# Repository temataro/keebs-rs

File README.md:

# Keebs 'R Us

Informal notes on me learning how to actually make this.
If you read this and you're not me, pretend you didn't.

The project template for the `rp2040-hal` is good.

To flash the code onto the uC, `probe-rs` is used.
  We'll just copy it over the old fashioned way since I don't have a debug probe.

Probes can translate from the USB/Ethernet interface on your computer to the
target interface.
(SWD for ARM, JTAG for ?..., etc)

_____________________________________________________________
We'll be using `elf2uf2-rs` which will convert the `.elf` file we generate to
binary targets for the cortex-m0+ uC. Loading a `.uf2` over USB.

Hold down the `BOOT` button on the uC while connecting to the PC and upload.
The pico should automatically get mounted on Linux.
It's found in `/run/media/tem`

> [!IMPORTANT]
> Go to `.cargo/config` and change the default runner 

#### <callout> `.cargo/config.toml`
```toml
[target.`cfg(all(target-arch = "arm", target_os = "none"))`]
runner = "elf2uf2-rs -d"
```

_____________________________________________________________
(Alternate): Look into `picotool`. The `elf` produced by Rust should be compatible
with the output that it takes. Just append a `.elf` to the binary.

### Requirements:

* rustup
* thumbv6m-none-eabi toolchain
* elf2uf2-rs

### Bare minimum file structure in your project

```
.
|-> Cargo.toml
|-> .cargo/
    |-> config.toml
|
|-> src/
    |-> main.rs
```

```shell
rustup target install thumbv6m-none-eabi
cargo install --locked elf2uf2-rs
```

Running:
`cargo run` - debug build
`cargo run --release` - release build (Our runner (`elf2uf2-rs`) will build and
copy it to the RP2040.)

## Bootloader

So apparently there's a bootloader, and to write 256 bytes to it, we need to initialize
it. Use this snippet to do so.

#### <callout> `src/main.rs`
```rust
use rp2040_boot2;
#[link_section = ".boot2"]
#[used]
pub static BOOT_LOADER: [u8; 256] = rp2040_boot2::BOOT_LOADER_W25Q080;
```

## Cargo.toml

#### <callout> `Cargo.toml`
```toml
[package]
edition = "2021"
# We're using 2021 because `cargo build` errors with 2024. No stable version exists.
name = "Keebs-rs"
version = "0.1.0"
license = "MIT OR Apache-2.0"
author = "Tem soon but for now this is all rp-hal code..."

[dependencies]
cortex-m = "0.7"
cortex-m-rt = "0.7"
embedded-hal = { version = "1.0.0" }
rp2040-hal = { version="0.10", features=["rt", "critical-section-impl"] }
rp2040-boot2 = "0.3.0"
panic-halt = "0.2.0"

defmt = "0.3"
defmt-rtt = "0.4"
panic-probe = { version = "0.3", features = ["print-defmt"] }

rp-pico = "0.9"

# cargo build/run
[profile.dev]
codegen-units = 1
debug = 2
debug-assertions = true
incremental = false
opt-level = 3
overflow-checks = true

# cargo build/run --release
[profile.release]
codegen-units = 1
debug = 2
debug-assertions = false
incremental = false
lto = 'fat'
opt-level = 3
overflow-checks = false

# do not optimize proc-macro crates = faster builds from scratch
[profile.dev.build-override]
codegen-units = 8
debug = false
debug-assertions = false
opt-level = 0
overflow-checks = false

[profile.release.build-override]
codegen-units = 8
debug = false
debug-assertions = false
opt-level = 0
overflow-checks = false

# cargo test
[profile.test]
codegen-units = 1
debug = 2
debug-assertions = true
incremental = false
opt-level = 3
overflow-checks = true

# cargo test --release
[profile.bench]
codegen-units = 1
debug = 2
debug-assertions = false
incremental = false
lto = 'fat'
opt-level = 3
```

## The Bare Minimum to Include

Goal: GPIO25 is the onboard green LED.
Make blinky.

Req. 1) #![no_std]
  - Can only use the core features of Rust, no fancy std features in embedded.

Req. 2) #![no_main]
  - Define your entry point like a man. No main as default entry for your code.

Req. 3) Crates and aliases
  - Introduce crates for `panic_halt`, `rp2040_hal`
  - We need `rp2040_hal::pac` (Peripheral Access Crate)

#### <callout> `src/main.rs`

```rust
// File starts here
#![no_std]
#![no_main]

// Ensure we halt the program on panic (if we don't mention this crate it won't
// be linked)
use panic_halt as _;

// Alias for our HAL crate
use rp2040_hal as hal;

// A shorter alias for the Peripheral Access Crate, which provides low-level
// register access
use hal::pac;
```

Req. 4) Embedded Traits
  - Need these to 
    - do delay,
    - define input and output pins,
  
```rust
// Cont'd
// Apparently not needed for blinky, we use other pins???
use embedded_hal::delay::DelayNs;
use embedded_hal::digital::OutputPin; // or digital::{InputPin, OutputPin} for both
```

Req. 5) The bootloader
  - We've talked about this

```rust
// Cont'd

use rp2040_boot2;
#[link_section = ".boot2"]
#[used]
pub static BOOT_LOADER: [u8; 256] = rp2040_boot2::BOOT_LOADER_W25Q080;
```

Req. 6) Clock stuff
  - Define the crystal's frequency
      - RP2040 by default takes 12MHz, we'll probably buy a 12MHz crystal also...

```rust
// Cont'd
const XTAL_FREQ_HZ: u32 = 12_000_000u32;
```

  - We'll also need to configure clocks later with `hal::clocks::init_clocks_and_plls()`
  - Watchdog timer (to make sure the uC doesn't go in an infinite loop?)

Req. 7) Entry

```rust
// Cont'd
#[rp2040_hal::entry]
fn main() -> ! {
 // Main doesn't return anything.

  // This actually goes last, after everything has been initialized
  loop {
    // Loopy things go here
    led_pin.set_high().unwrap();
    timer.delay_ms(500);
    led_pin.set_low().unwrap();
    timer.delay_ms(500);
  }
}
```

Req. 8) Initialize PAC Peripherals, watchdog, and clocks
```rust
// Inside main function
let mut pac = pac::Peripherals::take().unwrap(); // Handle errors if take() fails
let mut watchdog = hal::Watchdog::new(pac.WATCHDOG);

let clocks = hal::clocks::init_clocks_and_plls(
  XTAL_FREQ_HZ,  
  pac.XOSC,
  pac.CLOCKS,
  pac.PLL_SYS,
  pac.PLL_USB,
  &mut pac.RESETS,
  &mut watchdog,
)
.unwrap();
```

Req. 9) Timer
```rust
// Inside main function
// Requires pac, clocks and watchdogs before init
let mut timer = rp2040_hal::Timer::new(pac.Timer, &mut pac.RESETS, &clocks);
```

Req. 10) SIO: Single-Cycle I/O
```rust
// Inside main function
// Requires pac singleton before init
let sio = hal::Sio::new(pac.SIO);
```

Req. 11) Pins
```rust
// Inside main function
let pins = hal::gpio::Pins::new(
  pac.IO_BANK0,
  pac.PADS_BANK0,
  sio.gpio_bank0,
  &mut pac.RESETS,
);
```

// TODO: Actually paste the function prototypes for all these functions
// Timer::new(), Pins::new(), clocks::init_clocks_and_plls(), Sio::new()
// Peripherals::take(), Watchdog::new(), gpio::Pins::new()

#### Finally,
Now that we have a clock (from our timer, PAC, and watchdog), and GPIO pins
(from SIO and PAC), we can configure a specific GPIO pin as output and blink'er.

// TODO: Make a list of all the functions in the pins module
```rust
// After all the inits
let mut led_pin = pins.gpio25.into_push_pull_output();
```

### Notes

Defining the dependencies on `rp2040_hal`, `rp2040_boot2`, and `panic_halt` NEEDS a `-` between the words
but it has to be a `_` in the main function!!!!
WHATTTT????

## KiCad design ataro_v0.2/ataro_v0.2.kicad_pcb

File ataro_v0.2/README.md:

Kicad 3D view

Assembled board:

Soldered with Epomaker Budgerigar switches, and LL4148 MELF diodes.
Using a cheap Arduino Pro Micro clone from aliexpress as the microcontroller.

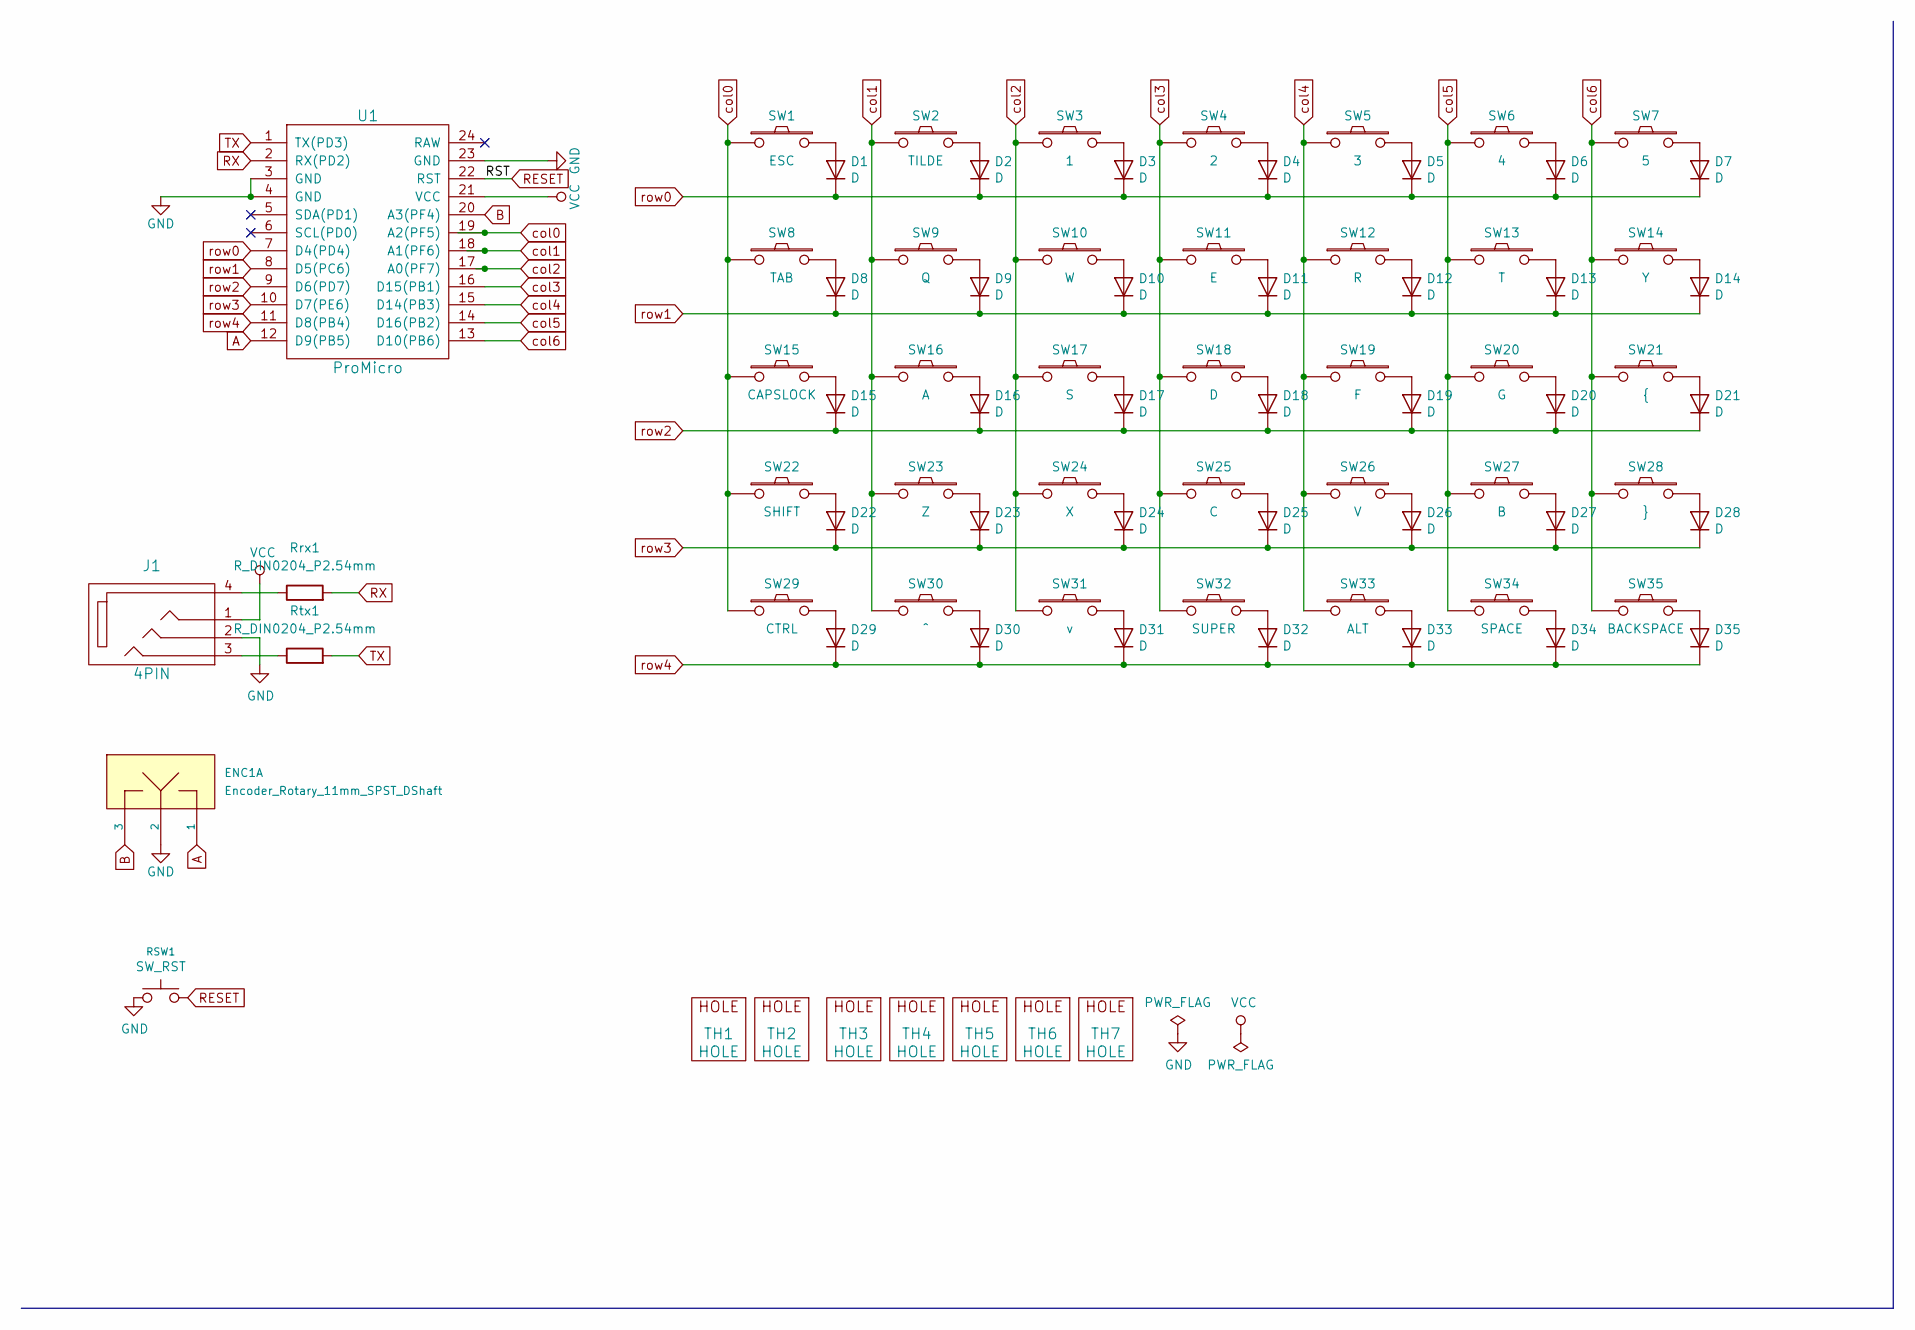
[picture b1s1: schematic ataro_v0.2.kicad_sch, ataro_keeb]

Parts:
D1, D2, D3, D4, D5, D6, D7, D8, D9, D10, D11, D12, D13, D14, D15, D16, D17, D18, D19, D20, D21, D22, D23, D24, D25, D26, D27, D28, D29, D30, D31, D32, D33, D34, D35: D; Diode_SOD-123
ENC1: Encoder_Rotary_11mm_SPST_DShaft; ENC_SPST_12mm; Part Number RE111F-41B3N-20F-20P-N
J1: 4PIN; TRRS_PJ-320A
RSW1: SW_RST; SW_PUSH_6mm_H13mm
Rrx1: R_DIN0204_P2.54mm; R_Axial_DIN0204_L3.6mm_D1.6mm_P1.90mm_Vertical
Rtx1: R_DIN0204_P2.54mm; R_Axial_DIN0204_L3.6mm_D1.6mm_P1.90mm_Vertical
SW1: ESC; MX_PCB_1.25u
SW2: TILDE; MX_PCB_1.00u_Reversable
SW3: 1; MX_PCB_1.00u_Reversable
SW4: 2; MX_PCB_1.00u_Reversable
SW5: 3; MX_PCB_1.00u_Reversable
SW6: 4; MX_PCB_1.00u_Reversable
SW7: 5; MX_PCB_1.00u_Reversable
SW8: TAB; MX_PCB_1.50u
SW9: Q; MX_PCB_1.00u_Reversable
SW10: W; MX_PCB_1.00u_Reversable
SW11: E; MX_PCB_1.00u_Reversable
SW12: R; MX_PCB_1.00u_Reversable
SW13: T; MX_PCB_1.00u_Reversable
SW14: Y; MX_PCB_1.00u_Reversable
SW15: CAPSLOCK; MX_PCB_1.75u
SW16: A; MX_PCB_1.00u_Reversable
SW17: S; MX_PCB_1.00u_Reversable
SW18: D; MX_PCB_1.00u_Reversable
SW19: F; MX_PCB_1.00u_Reversable
SW20: G; MX_PCB_1.00u_Reversable
SW21: {; MX_PCB_1.00u_Reversable
SW22: SHIFT; MX_PCB_1.75u
SW23: Z; MX_PCB_1.00u_Reversable
SW24: X; MX_PCB_1.00u_Reversable
SW25: C; MX_PCB_1.00u_Reversable
SW26: V; MX_PCB_1.00u_Reversable
SW27: B; MX_PCB_1.00u_Reversable
SW28: }; MX_PCB_1.00u_Reversable
SW29: CTRL; MX_PCB_1.25u
SW30: ^; MX_PCB_1.00u_Reversable
SW31: v; MX_PCB_1.00u_Reversable
SW32: SUPER; MX_PCB_1.25u
SW33: ALT; MX_PCB_1.25u
SW34: SPACE; MX_PCB_2.00u
SW35: BACKSPACE; MX_PCB_2.00u
TH1, TH2: HOLE; HOLE_M2
TH3, TH4, TH5, TH6, TH7: HOLE; HOLE_M2_TH
U1: ProMicro; Arduino_Pro_Micro

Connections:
A: ENC1.1, U1.12 (D9(PB5))
B: ENC1.3, U1.20 (A3(PF4))
GND: ENC1.2, J1.2, RSW1.1, U1.3 (GND), U1.4 (GND), U1.23 (GND)
unnamed: D1.2 (A), SW1.2
unnamed: D2.2 (A), SW2.2
unnamed: D3.2 (A), SW3.2
unnamed: D4.2 (A), SW4.2
unnamed: D5.2 (A), SW5.2
unnamed: D6.2 (A), SW6.2
unnamed: D7.2 (A), SW7.2
unnamed: D8.2 (A), SW8.2
unnamed: D9.2 (A), SW9.2
unnamed: D10.2 (A), SW10.2
unnamed: D11.2 (A), SW11.2
unnamed: D12.2 (A), SW12.2
unnamed: D13.2 (A), SW13.2
unnamed: D14.2 (A), SW14.2
unnamed: D15.2 (A), SW15.2
unnamed: D16.2 (A), SW16.2
unnamed: D17.2 (A), SW17.2
unnamed: D18.2 (A), SW18.2
unnamed: D19.2 (A), SW19.2
unnamed: D20.2 (A), SW20.2
unnamed: D21.2 (A), SW21.2
unnamed: D22.2 (A), SW22.2
unnamed: D23.2 (A), SW23.2
unnamed: D24.2 (A), SW24.2
unnamed: D25.2 (A), SW25.2
unnamed: D26.2 (A), SW26.2
unnamed: D27.2 (A), SW27.2
unnamed: D28.2 (A), SW28.2
unnamed: D29.2 (A), SW29.2
unnamed: D30.2 (A), SW30.2
unnamed: D31.2 (A), SW31.2
unnamed: D32.2 (A), SW32.2
unnamed: D33.2 (A), SW33.2
unnamed: D34.2 (A), SW34.2
unnamed: D35.2 (A), SW35.2
unnamed: J1.3, Rtx1.1
unnamed: J1.4, Rrx1.1
RESET: RSW1.2, U1.22 (RST)
RX: Rrx1.2, U1.2 (RX(PD2))
TX: Rtx1.2, U1.1 (TX(PD3))
VCC: J1.1, U1.21 (VCC)
col0: SW1.1, SW8.1, SW15.1, SW22.1, SW29.1, U1.19 (A2(PF5))
col1: SW2.1, SW9.1, SW16.1, SW23.1, SW30.1, U1.18 (A1(PF6))
col2: SW3.1, SW10.1, SW17.1, SW24.1, SW31.1, U1.17 (A0(PF7))
col3: SW4.1, SW11.1, SW18.1, SW25.1, SW32.1, U1.16 (D15(PB1))
col4: SW5.1, SW12.1, SW19.1, SW26.1, SW33.1, U1.15 (D14(PB3))
col5: SW6.1, SW13.1, SW20.1, SW27.1, SW34.1, U1.14 (D16(PB2))
col6: SW7.1, SW14.1, SW21.1, SW28.1, SW35.1, U1.13 (D10(PB6))
row0: D1.1 (K), D2.1 (K), D3.1 (K), D4.1 (K), D5.1 (K), D6.1 (K), D7.1 (K), U1.7 (D4(PD4))
row1: D8.1 (K), D9.1 (K), D10.1 (K), D11.1 (K), D12.1 (K), D13.1 (K), D14.1 (K), U1.8 (D5(PC6))
row2: D15.1 (K), D16.1 (K), D17.1 (K), D18.1 (K), D19.1 (K), D20.1 (K), D21.1 (K), U1.9 (D6(PD7))
row3: D22.1 (K), D23.1 (K), D24.1 (K), D25.1 (K), D26.1 (K), D27.1 (K), D28.1 (K), U1.10 (D7(PE6))
row4: D29.1 (K), D30.1 (K), D31.1 (K), D32.1 (K), D33.1 (K), D34.1 (K), D35.1 (K), U1.11 (D8(PB4))

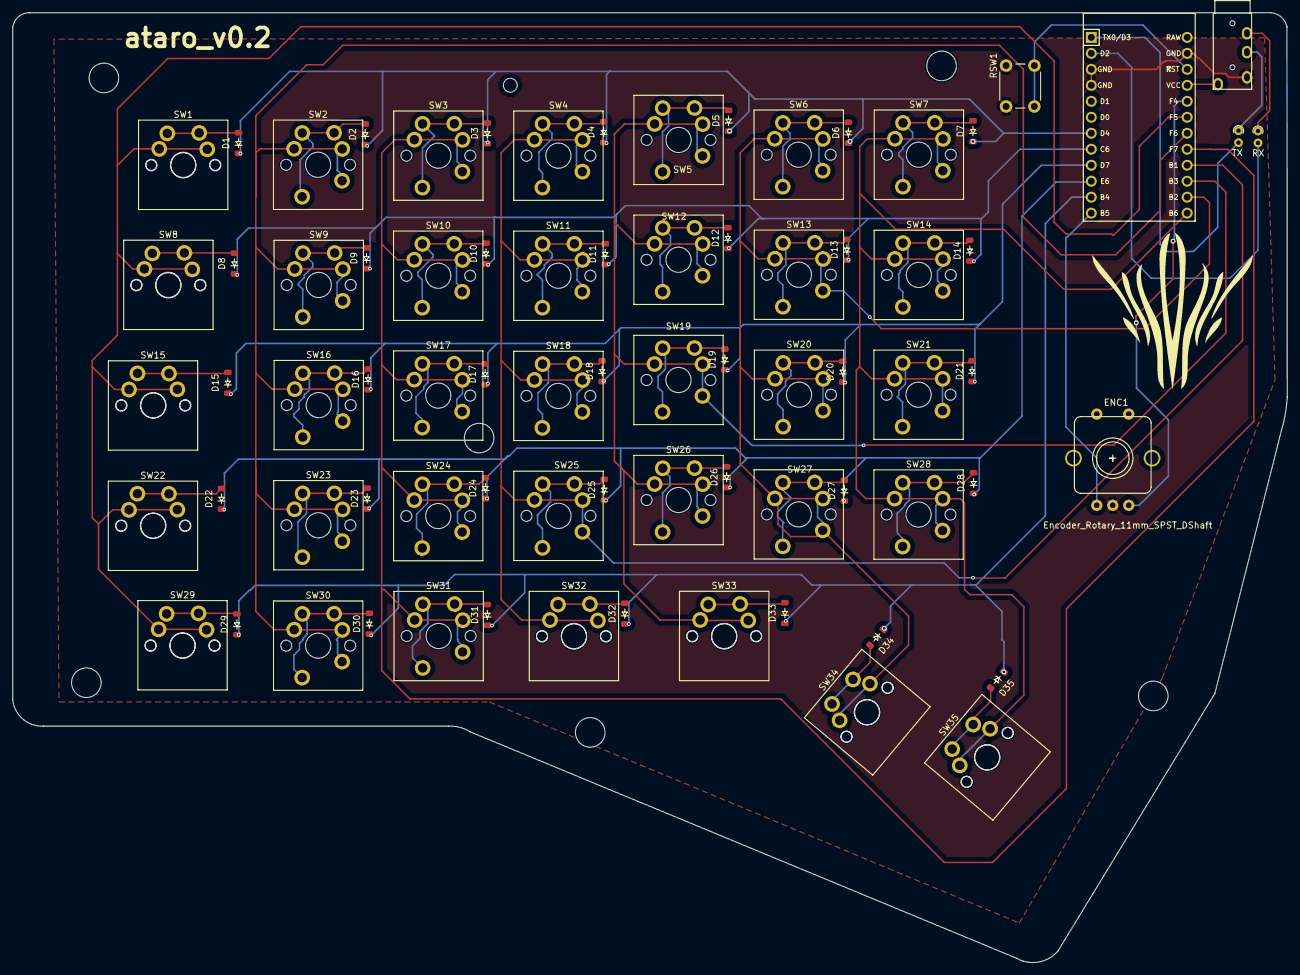
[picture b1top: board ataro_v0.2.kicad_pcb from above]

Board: 4 copper layers, 202.6 x 151.0 mm, 83 parts (0 on the bottom side), 56 nets.

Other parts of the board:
TH4#2: HOLE; HOLE_M2_TH

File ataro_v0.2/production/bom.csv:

Designator,Footprint,Quantity,Value,LCSC Part #
"D1, D10, D11, D12, D13, D14, D15, D16, D17, D18, D19, D2, D20, D21, D22, D23, D24, D25, D26, D27, D28, D29, D3, D30, D31, D32, D33, D34, D35, D4, D5, D6, D7, D8, D9",Diode_SOD-123,35,D,
ENC1,ENC_SPST_12mm,1,Encoder_Rotary_11mm_SPST_DShaft,
J1,TRRS_PJ-320A,1,4PIN,
RSW1,SW_PUSH_6mm_H13mm,1,SW_RST,
"Rrx1, Rtx1",R_Axial_DIN0204_L3.6mm_D1.6mm_P1.90mm_Vertical,2,R_DIN0204_P2.54mm,
SW1,MX_PCB_1.25u,1,ESC,
SW10,MX_PCB_1.00u_Reversable,1,W,
SW11,MX_PCB_1.00u_Reversable,1,E,
SW12,MX_PCB_1.00u_Reversable,1,R,
SW13,MX_PCB_1.00u_Reversable,1,T,
SW14,MX_PCB_1.00u_Reversable,1,Y,
SW15,MX_PCB_1.75u,1,CAPSLOCK,
SW16,MX_PCB_1.00u_Reversable,1,A,
SW17,MX_PCB_1.00u_Reversable,1,S,
SW18,MX_PCB_1.00u_Reversable,1,D,
SW19,MX_PCB_1.00u_Reversable,1,F,
SW2,MX_PCB_1.00u_Reversable,1,TILDE,
SW20,MX_PCB_1.00u_Reversable,1,G,
SW21,MX_PCB_1.00u_Reversable,1,{,
SW22,MX_PCB_1.75u,1,SHIFT,
SW23,MX_PCB_1.00u_Reversable,1,Z,
SW24,MX_PCB_1.00u_Reversable,1,X,
SW25,MX_PCB_1.00u_Reversable,1,C,
"SW26, SW31",MX_PCB_1.00u_Reversable,2,V,
SW27,MX_PCB_1.00u_Reversable,1,B,
SW28,MX_PCB_1.00u_Reversable,1,},
SW29,MX_PCB_1.25u,1,CTRL,
SW3,MX_PCB_1.00u_Reversable,1,1,
SW30,MX_PCB_1.00u_Reversable,1,^,
SW32,MX_PCB_1.25u,1,SUPER,
SW33,MX_PCB_1.25u,1,ALT,
SW34,MX_PCB_2.00u,1,SPACE,
SW35,MX_PCB_2.00u,1,BACKSPACE,
SW4,MX_PCB_1.00u_Reversable,1,2,
SW5,MX_PCB_1.00u_Reversable,1,3,
SW6,MX_PCB_1.00u_Reversable,1,4,
SW7,MX_PCB_1.00u_Reversable,1,5,
SW8,MX_PCB_1.50u,1,TAB,
SW9,MX_PCB_1.00u_Reversable,1,Q,
TH2,HOLE_M2,1,HOLE,
"TH3, TH4_2, TH4, TH5, TH6, TH7",HOLE_M2_TH,6,HOLE,
U1,Arduino_Pro_Micro,1,ProMicro,

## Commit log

2024-08-12 Ready, Set, Go.
2024-08-12 Rename notes.md to README.md
2024-08-17 Allow panics to remain unwrapped
    Without the panic="abort" section of `Cargo.toml` (I've put the line
    in both the debug and release builds), Rust will attempt to unwrap
    all panics it finds, but it can't do that without the standard library
    so it will bitch.
    I've also seen people do this instead
    ```rust
2024-08-17 Rename crate to be in all underscores because rust
2024-08-17 Use delay_ns function of delay::DelayNs crate
2024-08-17 Confirm delay functions work
2024-08-17 Implement a unitary clock pulse called UNIT_DELAY
2024-08-17 Refactor src/main.rs
    We no longer need the extra hand holding comments
2024-08-21 Add PCB for keyboard prototype
2024-08-21 Fix README formatting
2024-11-13 Final iteration of v0.2 for JLCPCB prod
2024-11-13 Notes on v0.2
2024-11-13 Add more notes on the production output
2025-02-02 Update todo.md
    Move extra ideas I had on a whiteboard over to here.
